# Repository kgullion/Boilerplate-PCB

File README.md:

Boilerplate-PCB
===============

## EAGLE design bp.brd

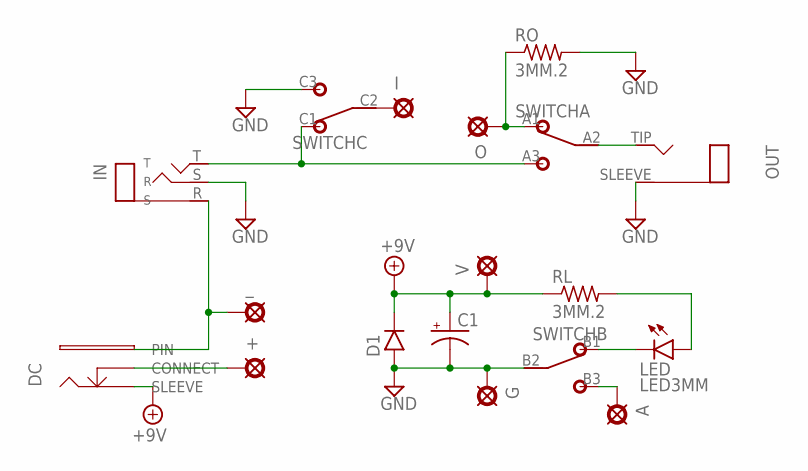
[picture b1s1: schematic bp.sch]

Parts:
+: PAD; SQUARE
A: PAD8; OCTOGON
C1: 0631; 063_025
D1: 1N400X.3; DO41-3
DC: DCP2; DC_PADS2
G: PADO; ROUND
I: PADO; ROUND
IN: STEREOP; STEREO_PADS
LED: LED3MM
O: PADO; ROUND
OUT: MONOP; TWO_PADS
RL: 3MM.2; R0204/2
RO: 3MM.2; R0204/2
SWITCH: 3PDTBLUE; CHINABLUE
V: PADO; ROUND
_: PADO; ROUND

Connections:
+9V: C1.+, D1.C, DC.S (SLEEVE), RL.1, V.1
GND: C1.-, D1.A, G.1, IN.S (R), OUT.SLEEVE, RO.2, SWITCH.B2 (2), SWITCH.C3 (3)
unnamed: OUT.TIP, SWITCH.A2 (2)
unnamed: IN.T, SWITCH.A3 (3), SWITCH.C1 (1)
unnamed: DC.P (PIN), IN.R (S), _.1
unnamed: LED.K (C), SWITCH.B1 (1)
unnamed: +.1, DC.C (CONNECT)
unnamed: LED.A, RL.2
unnamed: I.1, SWITCH.C2 (2)
unnamed: A.1, SWITCH.B3 (3)
unnamed: O.1, RO.1, SWITCH.A1 (1)

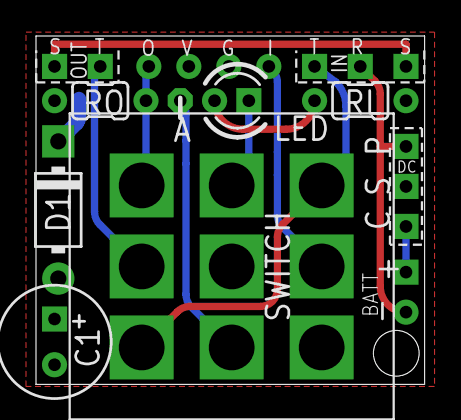
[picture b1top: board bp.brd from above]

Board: 2 copper layers, 21.6 x 19.4 mm, 16 parts (0 on the bottom side), 11 nets.

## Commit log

2014-05-30 init files
